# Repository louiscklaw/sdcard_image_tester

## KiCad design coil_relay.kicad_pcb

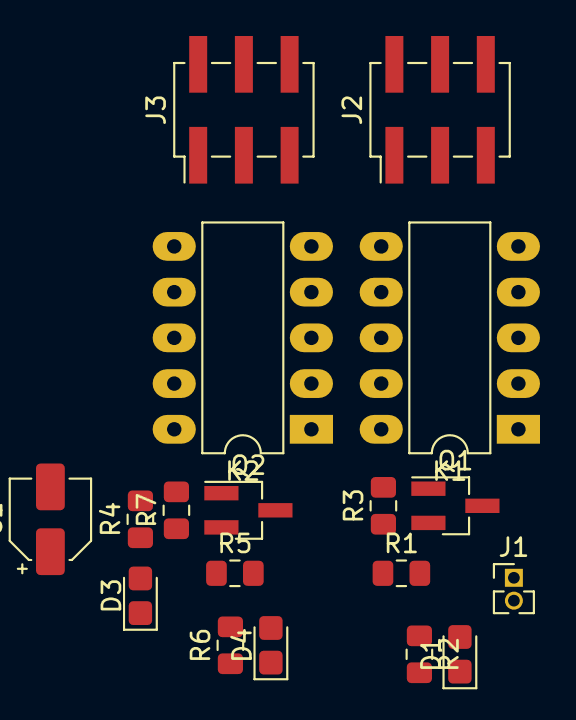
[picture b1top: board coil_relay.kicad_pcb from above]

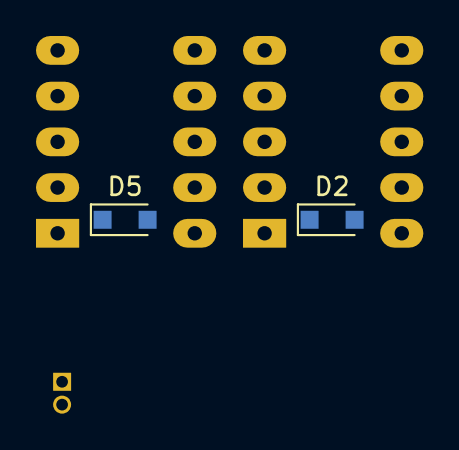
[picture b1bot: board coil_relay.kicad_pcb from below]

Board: 2 copper layers, 20 parts (2 on the bottom side), 23 nets, no tracks yet.

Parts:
C1: CP4.7uf,50V; CP_Elec_4x5.3
D1, D4: RELAY_STATUS; LED_0805_2012Metric_Castellated
D2, D5: 1N4148; D_SOD-323_HandSoldering
D3: 3V3_STATUS; LED_0805_2012Metric_Castellated
J1: Conn_01x02; PinHeader_1x02_P1.27mm_Vertical
J2, J3: Conn_02x03_Odd_Even; PinHeader_2x03_P2.54mm_Vertical_SMD
K1, K2: A5W-K; DIP-10_W7.62mm_LongPads
Q1, Q2: 2N3904(1AM); SOT-23_Handsoldering
R1, R2, R5, R6: 102; R_0805_2012Metric_Pad1.15x1.40mm_HandSolder
R3, R7: 103; R_0805_2012Metric_Pad1.15x1.40mm_HandSolder
R4: 511; R_0805_2012Metric_Pad1.15x1.40mm_HandSolder

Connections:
/R1_CH1_COM: J2.3, K1.3
/R1_CH1_NC: J2.1, K1.2
/R1_CH1_NO: J2.5, K1.4
/R1_CH2_COM: J2.4, K1.8
/R1_CH2_NC: J2.2, K1.9
/R1_CH2_NO: J2.6, K1.7
/R1_COIL_N: D1.1, D2.2, K1.10, Q1.3
/R1_CONTROL: J1.1, R1.2
/R2_CH1_COM: J3.3, K2.3
/R2_CH1_NC: J3.1, K2.2
/R2_CH1_NO: J3.5, K2.4
/R2_CH2_COM: J3.4, K2.8
/R2_CH2_NC: J3.2, K2.9
/R2_CH2_NO: J3.6, K2.7
/R2_COIL_N: D4.1, D5.2, K2.10, Q2.3
/R2_CONTROL: J1.2, R5.2
GND: C1.2, D3.1, Q1.2, Q2.2, R3.1, R7.1
unnamed: D1.2, R2.2
unnamed: D3.2, R4.1
unnamed: D4.2, R6.2
unnamed: Q1.1, R1.1, R3.2
unnamed: Q2.1, R5.1, R7.2
V_RELAY: C1.1, D2.1, D5.1, K1.1, K2.1, R2.1, R4.2, R6.1

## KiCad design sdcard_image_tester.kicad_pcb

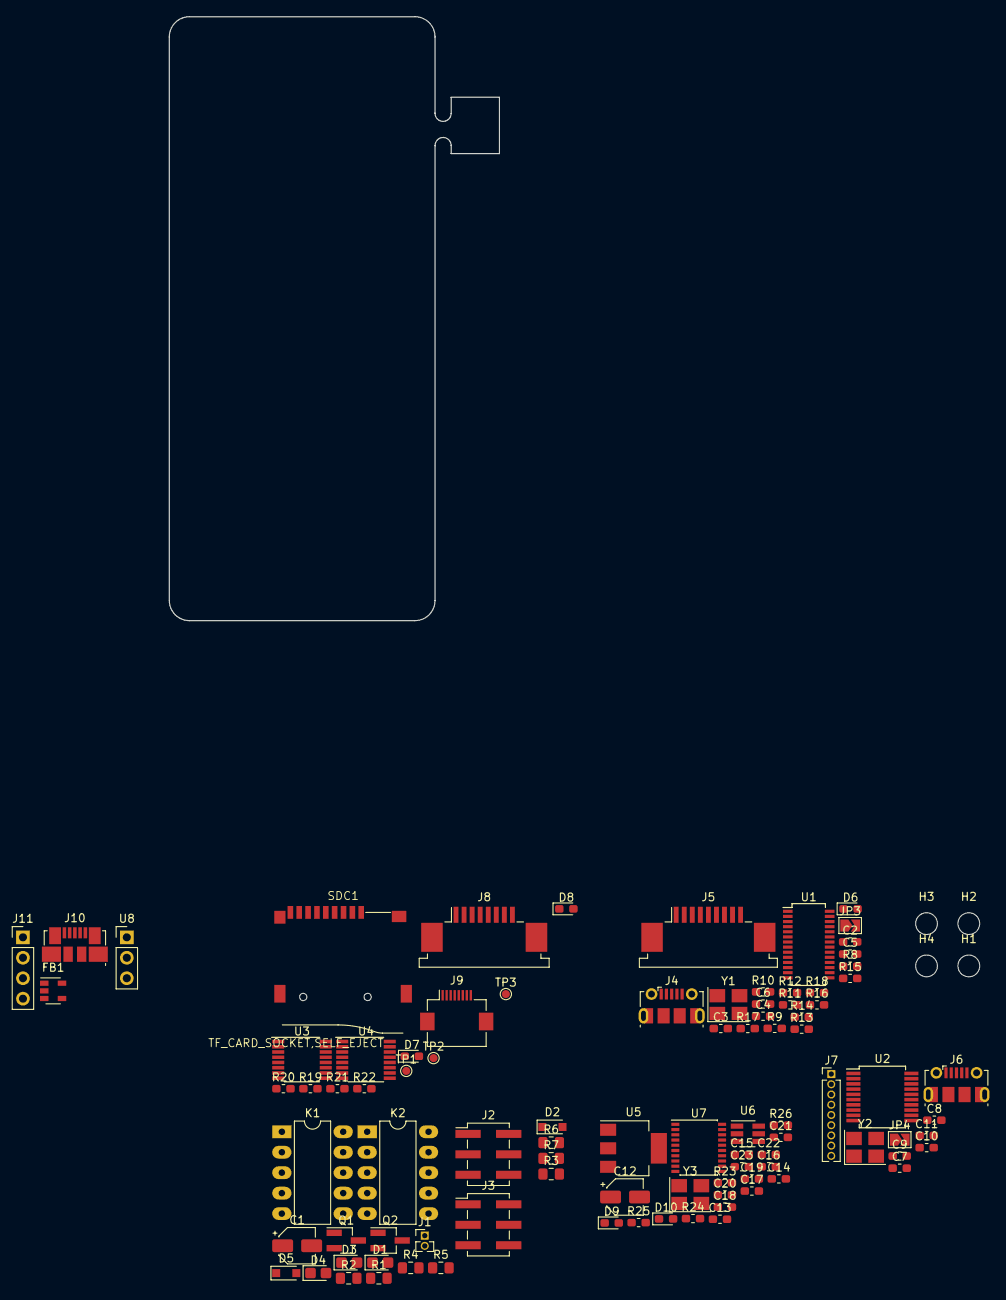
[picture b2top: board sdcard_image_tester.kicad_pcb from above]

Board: 2 copper layers, 41.0 x 75.0 mm, 96 parts (0 on the bottom side), 94 nets, no tracks yet.

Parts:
C1: CP4.7uf,50V; CP_Elec_4x5.3
C2, C3, C9, C10, C17, C18: C22pf,0603; C_0603_1608Metric_Pad1.05x0.95mm_HandSolder
C4, C5, C6, C8, C15, C19, C23: C104,0603; C_0603_1608Metric_Pad1.05x0.95mm_HandSolder
C7: C226,6.3v,0603; C_0603_1608Metric_Pad1.05x0.95mm_HandSolder
C11: C102,0603; C_0603_1608Metric_Pad1.05x0.95mm_HandSolder
C12: CP22uf,16V; CP_Elec_4x5.3
C13: C106,0603; C_0603_1608Metric_Pad1.05x0.95mm_HandSolder
C14, C20: C103,0603; C_0603_1608Metric_Pad1.05x0.95mm_HandSolder
C16, C22: C475,0603; C_0603_1608Metric_Pad1.05x0.95mm_HandSolder
C21: C105,0603; C_0603_1608Metric_Pad1.05x0.95mm_HandSolder
D1, D4: RELAY_STATUS; LED_0805_2012Metric_Castellated
D2, D5: 1N4148; D_SOD-323_HandSoldering
D3: 3V3_STATUS; LED_0805_2012Metric_Castellated
D6, D8, D9, D10: LED_GREEN,0603; LED_0603_1608Metric_Pad1.05x0.95mm_HandSolder
D7: LED_ORANGE,0603; LED_0603_1608Metric_Pad1.05x0.95mm_HandSolder
FB1: UPZ1608E221-2R2TF; SOT-23-5
H1, H2, H3, H4: MOUNT_M2.5; MountingHole_2.7mm_M2.5_DIN965
J1: Conn_01x02; PinHeader_1x02_P1.27mm_Vertical
J2, J3: Conn_02x03_Odd_Even; PinHeader_2x03_P2.54mm_Vertical_SMD
J4: USB_B_Micro; USB_Micro-B_Molex-105017-0001
J5: Conn_01x09; TE_84953-9_1x09-1MP_P1.0mm_Horizontal
J6: USB_B_Mini; USB_Micro-B_Molex-105017-0001
J7: Conn_01x09; PinHeader_1x09_P1.27mm_Vertical
J8: TO_PC; TE_84952-8_1x08-1MP_P1.0mm_Horizontal
J9: TO_DUT; Hirose_FH12-8S-0.5SH_1x08-1MP_P0.50mm_Horizontal
J10: USB_B_Micro; USB_Micro-B_Molex_47346-0001
J11: Conn_02x02_Odd_Even; PinHeader_1x04_P2.54mm_Vertical
JP3, JP4: SolderJumper_2_Open; SolderJumper-2_P1.3mm_Open_TrianglePad1.0x1.5mm
K1, K2: A5W-K; DIP-10_W7.62mm_LongPads
Q1, Q2: 2N3904(1AM); SOT-23_Handsoldering
R1, R2, R5, R6: 102; R_0805_2012Metric_Pad1.15x1.40mm_HandSolder
R3, R7: 103; R_0805_2012Metric_Pad1.15x1.40mm_HandSolder
R4: 511; R_0805_2012Metric_Pad1.15x1.40mm_HandSolder
R8, R9: R220,0603; R_0603_1608Metric_Pad1.05x0.95mm_HandSolder
R10, R21, R22, R26: R102,0603; R_0603_1608Metric_Pad1.05x0.95mm_HandSolder
R11, R12, R19, R20, R23: R103,0603; R_0603_1608Metric_Pad1.05x0.95mm_HandSolder
R13, R14, R15, R16, R17, R18: R473,0603; R_0603_1608Metric_Pad1.05x0.95mm_HandSolder
R24, R25: R104,0603; R_0603_1608Metric_Pad1.05x0.95mm_HandSolder
SDC1: TF_CARD_SOCKET,SELF_EJECT; SUNTECH_ST-TF-003A
TP1: VSD; TestPoint_Pad_D1.0mm
TP2: HS; TestPoint_Pad_D1.0mm
TP3: G; TestPoint_Pad_D1.0mm
U1: GL827L; SSOP-28_3.9x9.9mm_P0.635mm
U2: CH340T(SSOP20W); SSOP-20_5.3x7.2mm_P0.65mm
U3, U4: SN74CBT3257D; TSSOP-16_4.4x5mm_P0.65mm
U5: AMS1117-3.3; SOT-223-3_TabPin2
U6: USBLC6-2SC6; SOT-23-6_Handsoldering
U7: STM32F042F6P6; SSOP-20_4.4x6.5mm_P0.65mm
U8: swd-pinsocket; PinHeader_1x03_P2.54mm_Vertical
Y1, Y2: O_12M,3225; Oscillator_SMD_Abracon_ASE-4Pin_3.2x2.5mm_HandSoldering
Y3: O_8M,3225; Oscillator_SMD_Abracon_ASE-4Pin_3.2x2.5mm_HandSoldering

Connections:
+5V: C12.1, C15.1, C16.1, FB1.1, R23.1, U5.3
/STM32F042F6P6/BOOT0_SELECT: J11.1, J11.3, U7.1
/STM32F042F6P6/PA6: J1.2, R5.2, U7.12
/STM32F042F6P6/PA7: J1.1, R1.2, U7.13
/STM32F042F6P6/PA9: U6.4, U7.17
/STM32F042F6P6/PA10: U6.6, U7.18
/STM32F042F6P6/PA13: U7.19, U8.1
/STM32F042F6P6/PA14: U7.20, U8.3
/STM32F042F6P6/RESET: C19.2, R25.2, U7.4
/STM32F042F6P6/XIN: C17.1, U7.2, Y3.1
/STM32F042F6P6/XOUT: C18.1, U7.3, Y3.3
/ch340T/CH340_RXD: J7.2, U2.4, U7.8
/ch340T/CH340_TXD: J7.3, U2.3, U7.9
/ch340T/DTR: J7.8, U2.15
/ch340T/RTS: J7.9, U2.16
/ch340T/USB_DM: J6.2, U2.7
/ch340T/USB_DP: J6.3, U2.6
/coil_relay/R1_CH1_COM: J2.3, K1.3
/coil_relay/R1_CH1_NC: J2.1, K1.2
/coil_relay/R1_CH1_NO: J2.5, K1.4
/coil_relay/R1_CH2_COM: J2.4, K1.8
/coil_relay/R1_CH2_NC: J2.2, K1.9
/coil_relay/R1_CH2_NO: J2.6, K1.7
/coil_relay/R1_COIL_N: D1.1, D2.2, K1.10, Q1.3
/coil_relay/R2_CH1_COM: J3.3, K2.3
/coil_relay/R2_CH1_NC: J3.1, K2.2
/coil_relay/R2_CH1_NO: J3.5, K2.4
/coil_relay/R2_CH2_COM: J3.4, K2.8
/coil_relay/R2_CH2_NC: J3.2, K2.9
/coil_relay/R2_CH2_NO: J3.6, K2.7
/coil_relay/R2_COIL_N: D4.1, D5.2, K2.10, Q2.3
/sdcard_reader/ACTLED: R12.2, U1.28
/sdcard_reader/READER_DET: J5.9, U1.15
/sdcard_reader/USB_DM: R9.1, U1.9
/sdcard_reader/USB_DP: R8.1, U1.8
/sdcard_reader/X1: C2.1, U1.4, Y1.1
/sdcard_reader/X2: C3.1, U1.5, Y1.3
/sdcard_switch/CLK-Y: SDC1.5, U4.4
/sdcard_switch/CMD-Y: SDC1.3, U3.9
/sdcard_switch/DAT0-Y: SDC1.7, U4.9
/sdcard_switch/DAT1-Y: SDC1.8, U4.12
/sdcard_switch/DAT2-Y: SDC1.1, U3.4
/sdcard_switch/DAT3-Y: SDC1.2, U3.7
/sdcard_switch/DUT_CLK: J9.4, U4.2
/sdcard_switch/DUT_CMD: J9.6, U3.11
/sdcard_switch/DUT_DAT0: J9.2, U4.11
/sdcard_switch/DUT_DAT1: J9.1, U4.14
/sdcard_switch/DUT_DAT2: J9.8, U3.2
/sdcard_switch/DUT_DAT3: J9.7, U3.5
/sdcard_switch/DUT_VDD: J9.5, U3.14
/sdcard_switch/HOSTSELECT: R19.1, R21.1, TP2.1, U3.1, U4.1, U7.11
/sdcard_switch/OE: R20.2, U3.15, U4.15
/sdcard_switch/PC_CLK: J5.5, J8.5, R15.2, U1.20, U4.3
/sdcard_switch/PC_CMD: J5.3, J8.3, R16.2, U1.22, U3.10
/sdcard_switch/PC_DAT0: J5.7, J8.7, R14.2, U1.17, U4.10
/sdcard_switch/PC_DAT1: J5.8, J8.8, R13.2, U1.16, U4.13
/sdcard_switch/PC_DAT2: J5.1, J8.1, R18.2, U1.25, U3.3
/sdcard_switch/PC_DAT3: J5.2, J8.2, R17.2, U1.24, U3.6
/sdcard_switch/PC_VDD: J5.4, J8.4, U1.2, U3.13
/sdcard_switch/VDD-Y: SDC1.4, U3.12
GND: C1.2, C2.2, C3.2, C4.2, C5.2, C6.2, C7.1, C8.2, C9.1, C10.2, C11.2, C12.2, C13.2, C14.2, C15.2, C16.2, C17.2, C18.2, C19.1, C20.2, C21.2, C22.1, C23.1, D3.1, D6.1, D7.1, D8.1, D9.1, D10.1, J4.5, J4.6, J5.6, J6.5, J6.6, J7.1, J8.6, J9.3, J10.5, J10.6, J11.2, Q1.2, Q2.2, R3.1, R7.1, R10.2, R19.2, R20.1, R24.2, SDC1.6, SDC1.G, TP3.1, U1.6, U1.14, U2.8, U3.8, U4.5, U4.6, U4.8, U5.1, U6.2, U7.15, U8.2, Y1.2, Y2.2, Y3.2
unnamed: C6.1, R11.2, U1.13
unnamed: C9.2, U2.9, Y2.1
unnamed: C10.1, U2.10, Y2.3
unnamed: C11.1, U2.5
unnamed: C14.1, FB1.2, J10.1, U6.5
unnamed: D1.2, R2.2
unnamed: D3.2, R4.1
unnamed: D4.2, R6.2
unnamed: D6.2, R12.1
unnamed: D7.2, R21.2
unnamed: D8.2, R22.2
unnamed: D9.2, R23.2
unnamed: D10.2, R26.1
unnamed: J4.1, JP3.1
unnamed: J4.2, R9.2
unnamed: J4.3, R8.2
unnamed: J6.1, JP4.1
unnamed: J7.4, U2.11
unnamed: J7.5, U2.12
unnamed: J7.6, U2.13
unnamed: J7.7, U2.14
unnamed: J10.2, U6.3
unnamed: J10.3, U6.1
unnamed: J10.4, R24.1
unnamed: Q1.1, R1.1, R3.2
unnamed: Q2.1, R5.1, R7.2
unnamed: R10.1, U1.10
VDD_STM32: C13.1, C20.1, C21.1, C22.2, C23.2, J11.4, R25.1, R26.2, U5.2, U7.16
V_CH340: C7.2, C8.1, JP4.2, U2.19
V_RELAY: C1.1, D2.1, D5.1, K1.1, K2.1, R2.1, R4.2, R6.1
V_SDCARD_READER: C5.1, JP3.2, U1.12
V_SDCARD_READER_3V3: C4.1, R11.1, R13.1, R14.1, R15.1, R16.1, R17.1, R18.1, U1.3, U1.7, U1.11
V_SDCARD_SWITCH: R22.1, TP1.1, U3.16, U4.16

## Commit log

2019-01-01 init commit,
2019-01-01 collect schematic,
2019-01-01 update,
2019-01-01 udpate for .gitattributes,
